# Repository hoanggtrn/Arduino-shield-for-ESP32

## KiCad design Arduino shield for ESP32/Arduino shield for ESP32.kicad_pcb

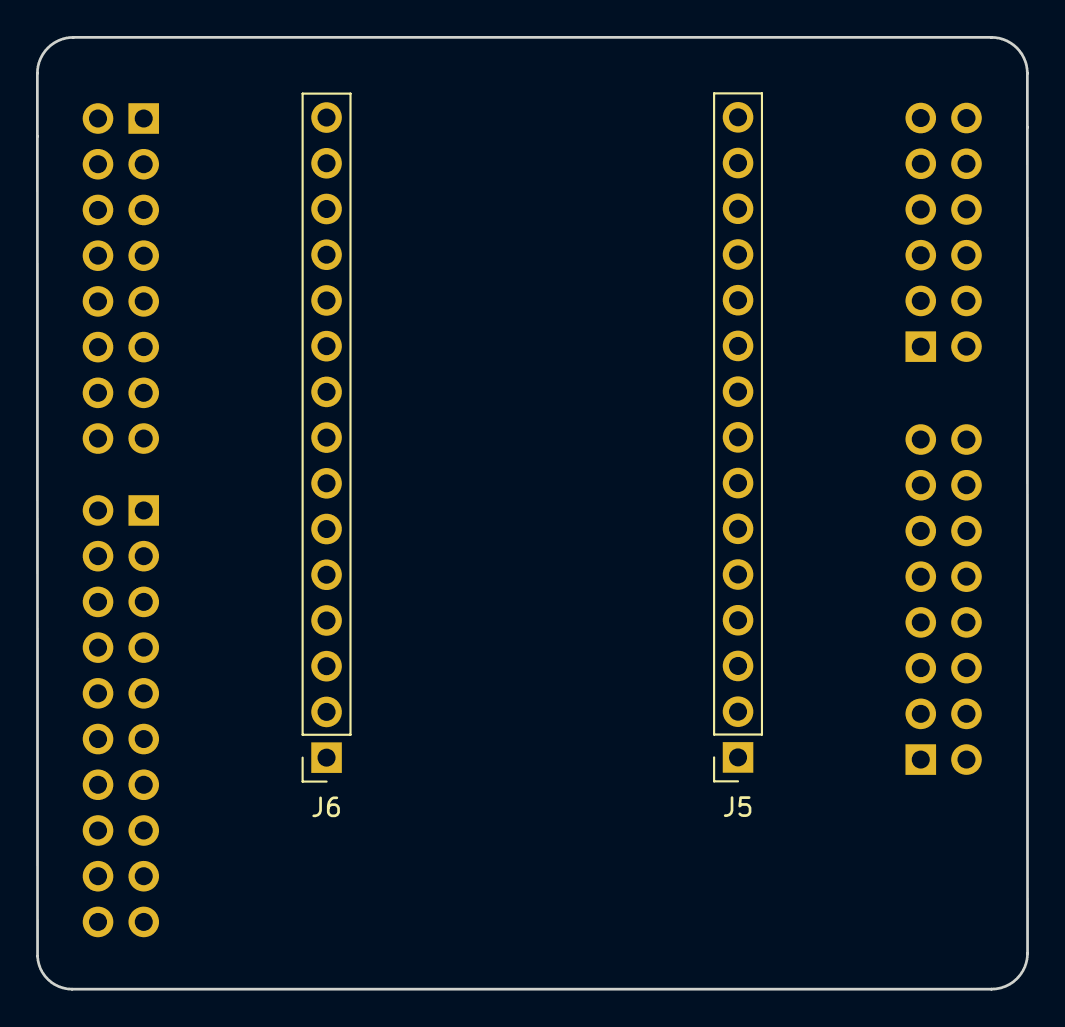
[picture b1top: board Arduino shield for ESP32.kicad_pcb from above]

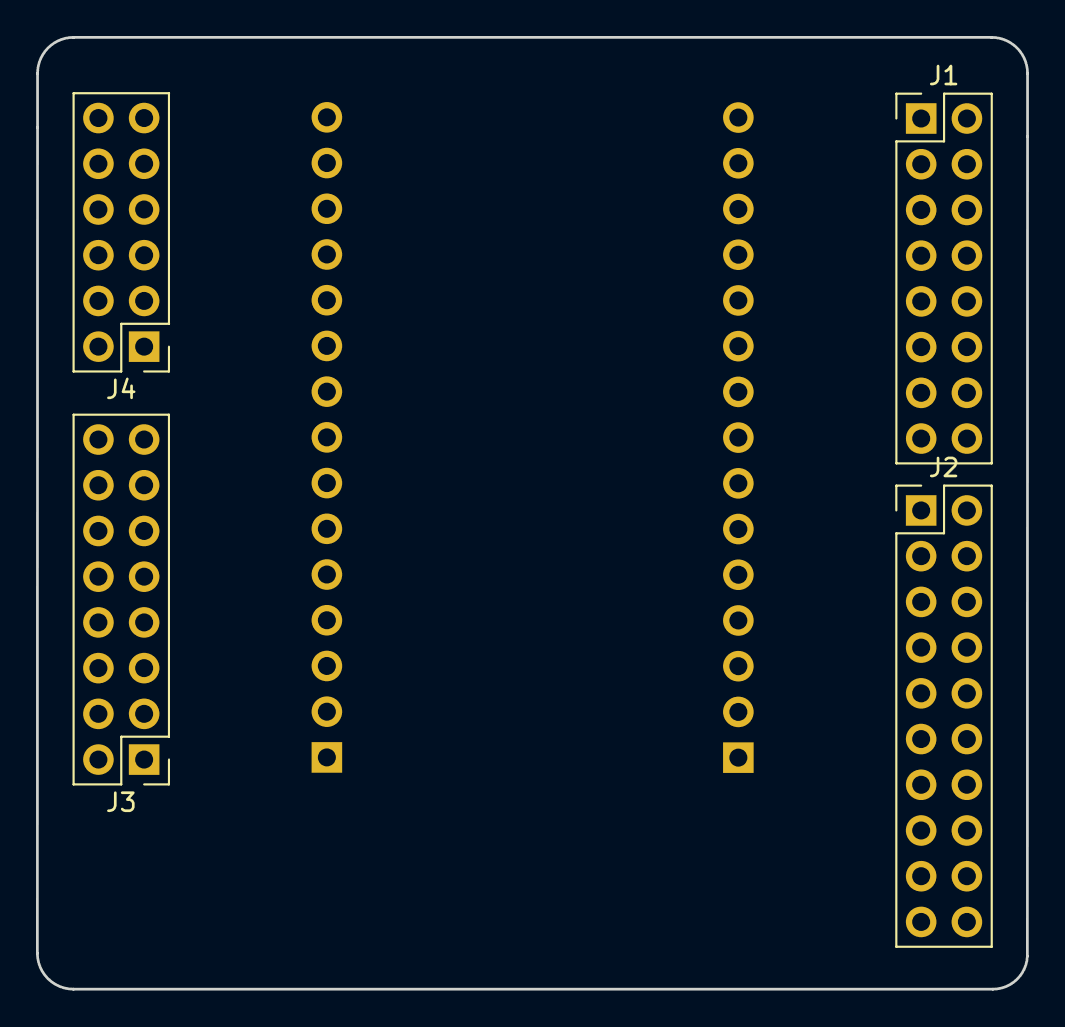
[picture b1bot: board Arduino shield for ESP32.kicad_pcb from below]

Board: 2 copper layers, 55.0 x 52.9 mm, 6 parts (4 on the bottom side), 10 nets, no tracks yet.

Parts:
J1, J3: Conn_02x08_Odd_Even; PinHeader_2x08_P2.54mm_Vertical
J2: Conn_02x10_Odd_Even; PinHeader_2x10_P2.54mm_Vertical
J4: Conn_02x06_Odd_Even; PinHeader_2x06_P2.54mm_Vertical
J5, J6: Conn_01x15; PinSocket_1x15_P2.54mm_Vertical

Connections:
/1: J2.1, J2.2, J2.3, J2.4, J2.5, J2.6, J2.7, J2.8, J2.9, J2.10, J2.11, J2.12, J2.13, J2.14, J2.15, J2.16, J2.17, J2.18, J2.19, J2.20, J3.2, J3.6, J4.1, J4.2, J4.3, J4.4, J4.5, J4.6, J4.7, J4.8, J4.9, J4.10, J4.11, J4.12
/3V3: J3.4, J3.8, J5.1
/5V: J3.10, J5.14
/GND: J3.12, J3.14, J5.15, J6.1, J6.10, J6.12, J6.15
SDIO_CLK: J3.11, J5.10
SDIO_CMD: J3.9, J5.11
SDIO_D0: J3.5, J5.9
SDIO_D1: J3.7, J5.8
SDIO_D2: J3.13, J6.13
SDIO_D3: J3.15, J6.14
